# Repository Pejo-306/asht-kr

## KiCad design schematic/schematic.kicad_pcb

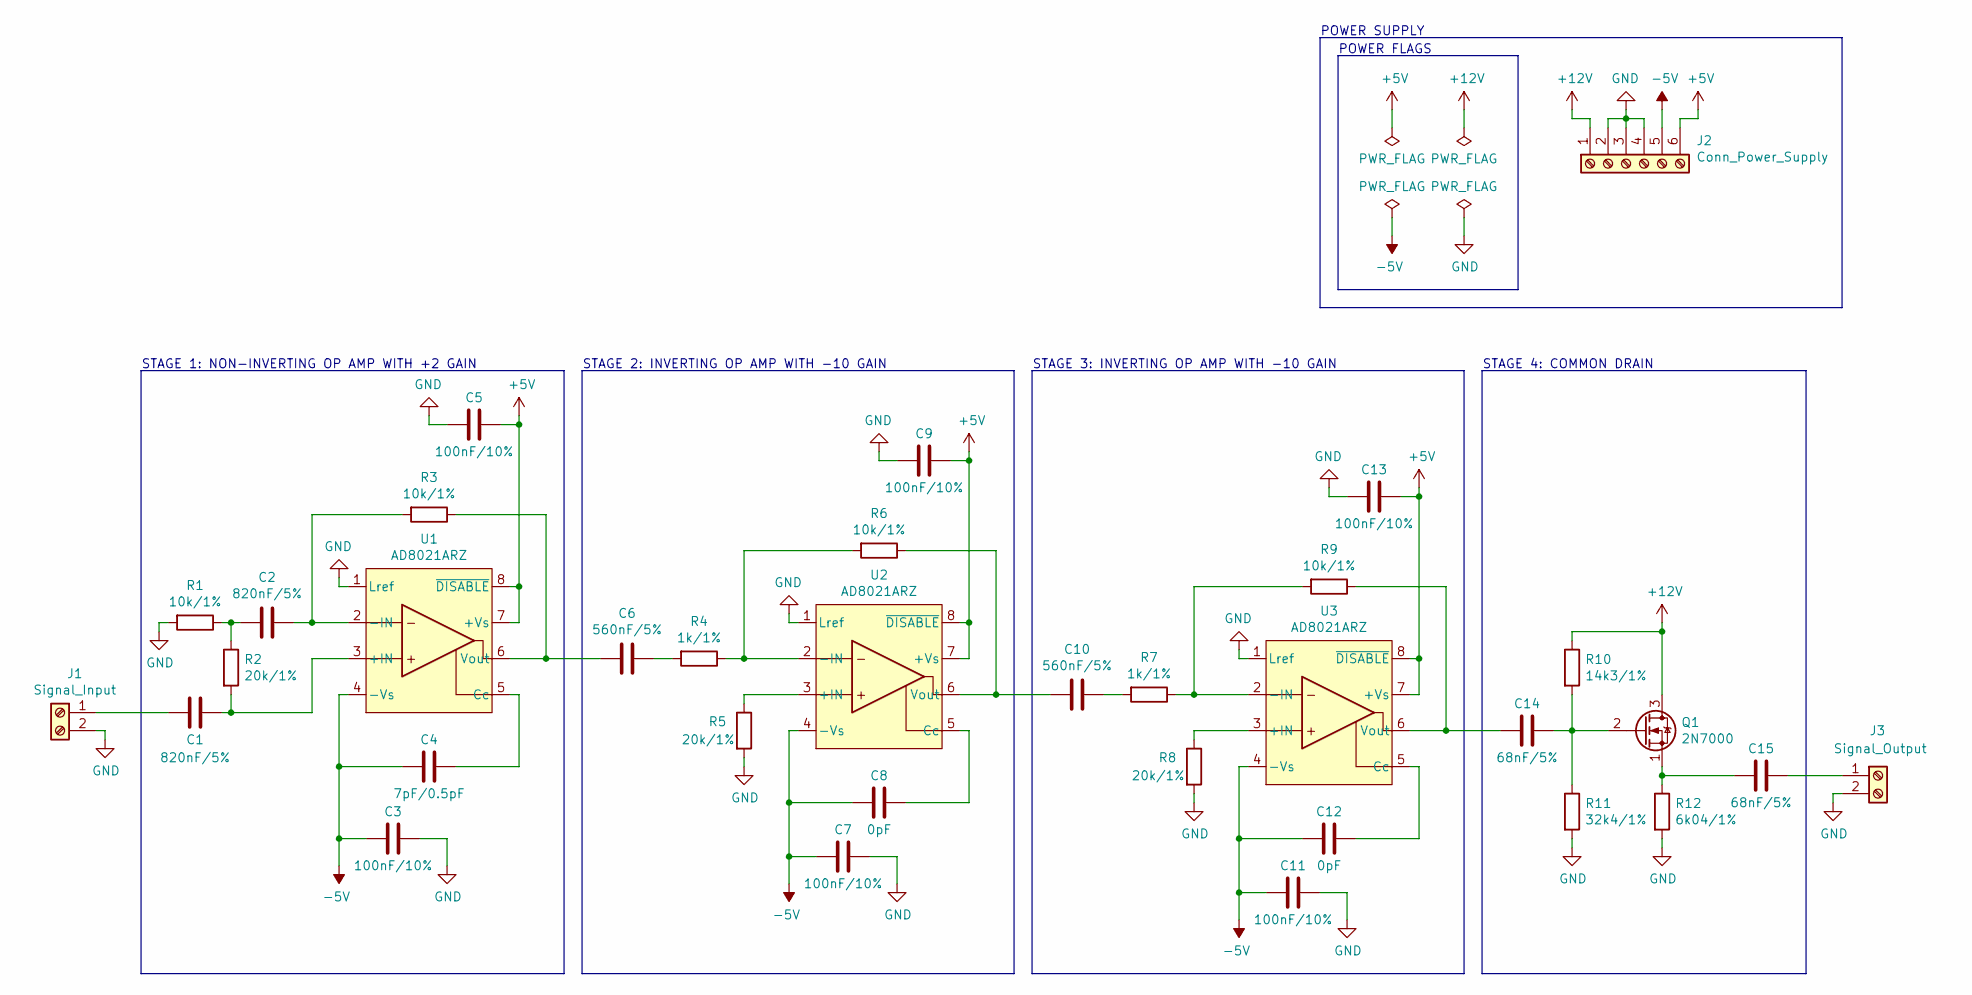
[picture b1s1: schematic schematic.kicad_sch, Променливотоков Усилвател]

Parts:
C1, C2: 820nF/5%; C_0603_1608Metric_Pad1.08x0.95mm_HandSolder
C3, C5, C7, C9, C11, C13: 100nF/10%; C_0603_1608Metric_Pad1.08x0.95mm_HandSolder
C4: 7pF/0.5pF; C_0603_1608Metric_Pad1.08x0.95mm_HandSolder
C6, C10: 560nF/5%; C_0603_1608Metric_Pad1.08x0.95mm_HandSolder
C8, C12: 0pF; C_0603_1608Metric_Pad1.08x0.95mm_HandSolder
C14, C15: 68nF/5%; C_0603_1608Metric_Pad1.08x0.95mm_HandSolder
J1: Signal_Input; TerminalBlock_bornier-2_P5.08mm
J2: Conn_Power_Supply; TerminalBlock_bornier-6_P5.08mm
J3: Signal_Output; TerminalBlock_bornier-2_P5.08mm
Q1: 2N7000; TO-92_Inline
R1, R3, R6, R9: 10k/1%; R_0603_1608Metric_Pad0.98x0.95mm_HandSolder
R2, R5, R8: 20k/1%; R_0603_1608Metric_Pad0.98x0.95mm_HandSolder
R4, R7: 1k/1%; R_0603_1608Metric_Pad0.98x0.95mm_HandSolder
R10: 14k3/1%; R_0603_1608Metric_Pad0.98x0.95mm_HandSolder
R11: 32k4/1%; R_0603_1608Metric_Pad0.98x0.95mm_HandSolder
R12: 6k04/1%; R_0603_1608Metric_Pad0.98x0.95mm_HandSolder
U1, U2, U3: AD8021ARZ; SOIC-8_3.9x4.9mm_P1.27mm

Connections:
+5V: C5.1, C9.1, C13.1, J2.6, U1.7 (+Vs), U1.8 (~DISABLE), U2.7 (+Vs), U2.8 (~DISABLE), U3.7 (+Vs), U3.8 (~DISABLE)
+12V: J2.1, Q1.3 (D), R10.1
-5V: C3.2, C4.2, C7.2, C8.2, C11.2, C12.2, J2.5, U1.4 (-Vs), U2.4 (-Vs), U3.4 (-Vs)
GND: C3.1, C5.2, C7.1, C9.2, C11.1, C13.2, J1.2, J2.2, J2.3, J2.4, J3.2, R1.2, R5.2, R8.2, R11.2, R12.2, U1.1 (Lref), U2.1 (Lref), U3.1 (Lref)
unnamed: C1.1, R2.2, U1.3 (+IN)
unnamed: C1.2, J1.1
unnamed: C2.1, R3.2, U1.2 (-IN)
unnamed: C2.2, R1.1, R2.1
unnamed: C4.1, U1.5 (Cc)
unnamed: C6.1, R4.2
unnamed: C6.2, R3.1, U1.6 (Vout)
unnamed: C8.1, U2.5 (Cc)
unnamed: C10.1, R7.2
unnamed: C10.2, R6.1, U2.6 (Vout)
unnamed: C12.1, U3.5 (Cc)
unnamed: C14.1, Q1.2 (G), R10.2, R11.1
unnamed: C14.2, R9.1, U3.6 (Vout)
unnamed: C15.1, J3.1
unnamed: C15.2, Q1.1 (S), R12.1
unnamed: R4.1, R6.2, U2.2 (-IN)
unnamed: R5.1, U2.3 (+IN)
unnamed: R7.1, R9.2, U3.2 (-IN)
unnamed: R8.1, U3.3 (+IN)

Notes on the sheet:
STAGE 1: NON-INVERTING OP AMP WITH +2 GAIN
STAGE 4: COMMON DRAIN
STAGE 2: INVERTING OP AMP WITH -10 GAIN
POWER SUPPLY
STAGE 3: INVERTING OP AMP WITH -10 GAIN
POWER FLAGS

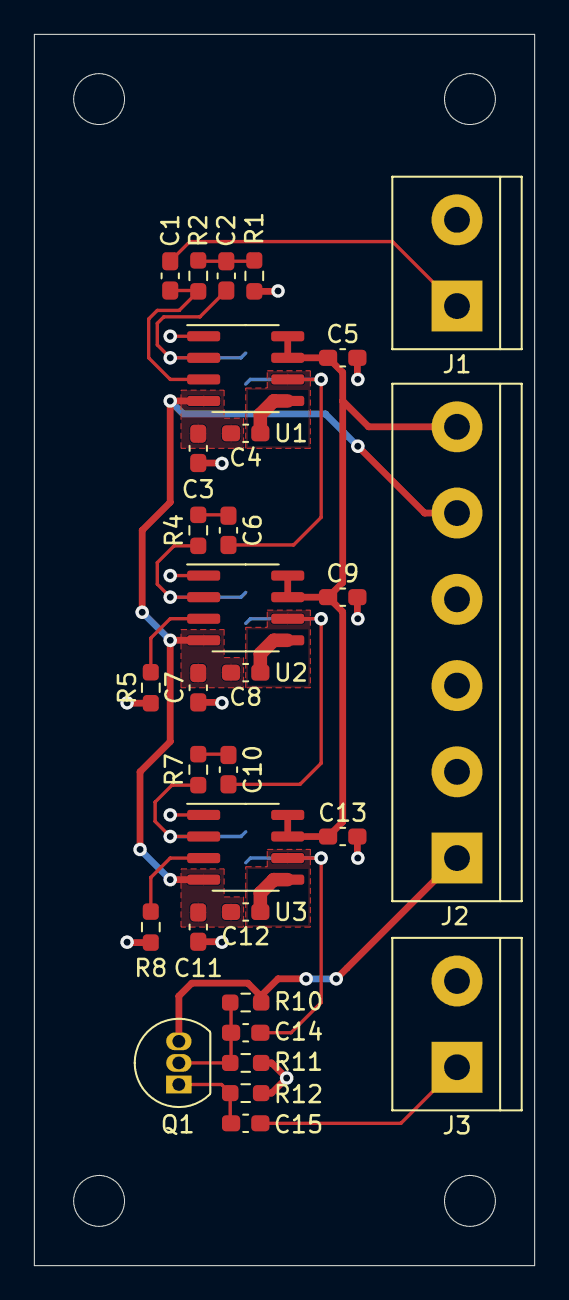
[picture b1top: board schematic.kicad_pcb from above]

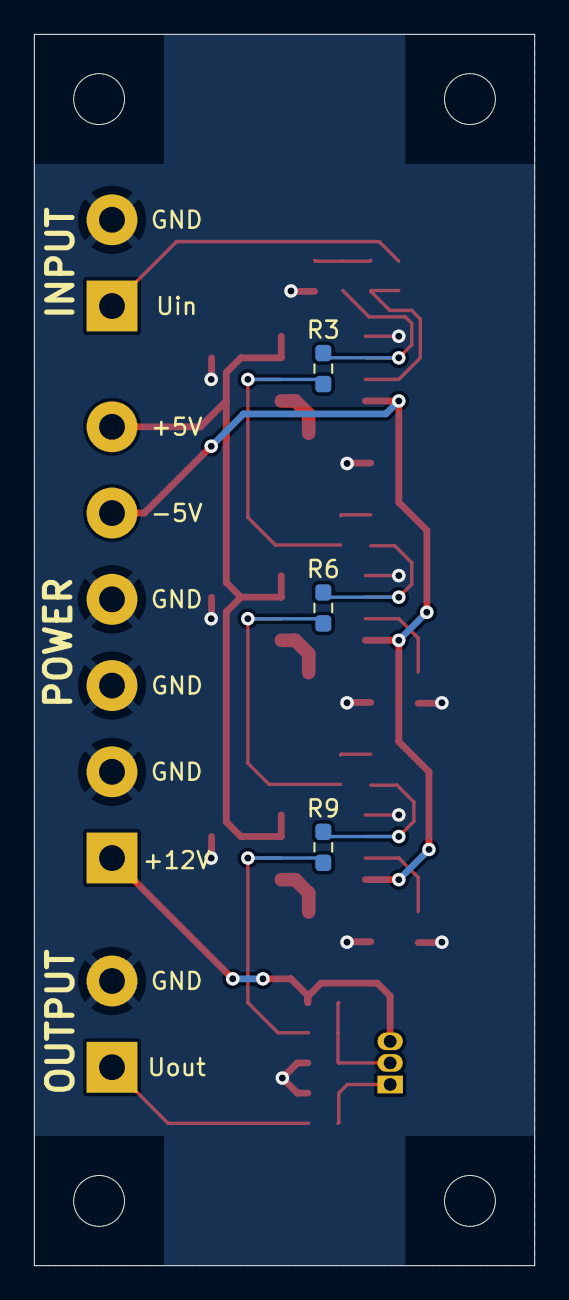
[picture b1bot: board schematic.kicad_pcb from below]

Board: 2 copper layers, 29.5 x 72.5 mm, 34 parts (3 on the bottom side), 23 nets.

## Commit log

2022-03-13 Create LICENSE
2022-03-13 Draw block diagram
2022-03-14 Add calculations
2022-03-19 Add power supply to block diagram
2022-03-22 Finish calculations
2022-03-22 Add stage 1 Spice circuit
2022-03-22 Add stage 4 circuit
2022-04-03 [Simulation] Add AD8021 subcircuit and symbol
2022-04-03 [Simulations] Add Stage 1 Spice schematic
2022-04-03 [Simulations] Add stage 2 Spice schematic
2022-04-03 [Simulation] Add stage 3 Spice schematic
2022-04-03 update stage 3
2022-04-03 [Simulations] Add stage 4 Spice schematic
2022-04-03 [Block diagram] Finish block diagram
2022-04-03 [Calculations] Finish calculations
2022-04-27 [Schematic] Upload KiCad electrical schematic
2022-04-27 [Simulations] Add Monte Carlo and other simulations for Stage 2
2022-04-27 [Schematic] Use screw terminal for signal output
2022-04-27 [Schematic] Associate symbols with footprints
2022-05-05 [PCB] Add PCB design
2022-05-05 [PCB] Flip power connector
2022-05-11 [Docs] Add project documentation
